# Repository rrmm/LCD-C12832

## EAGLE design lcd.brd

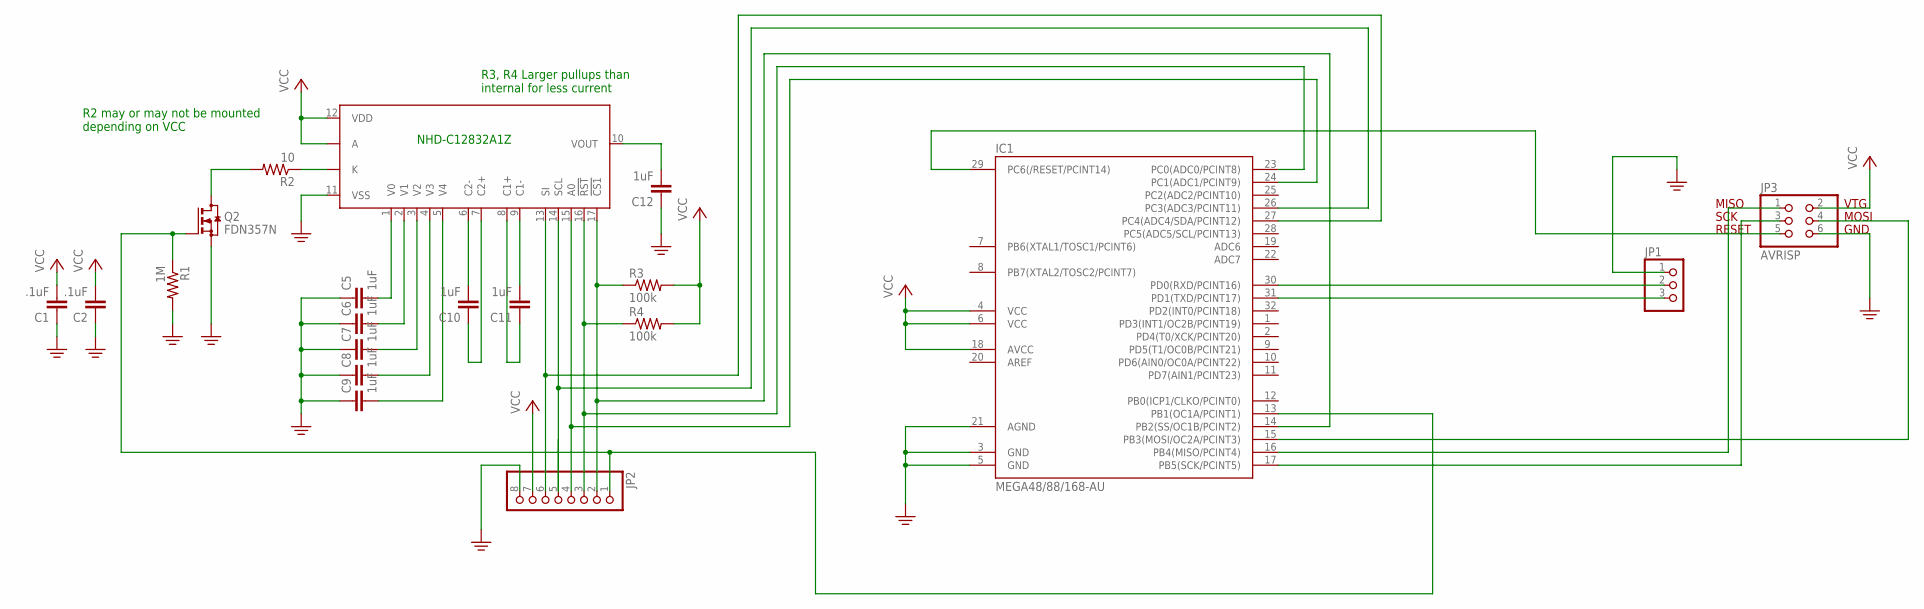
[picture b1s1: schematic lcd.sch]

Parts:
C1, C2: .1uF; C0603
C5, C6, C7, C8, C9, C10, C11, C12: 1uF; C0603
IC1: MEGA48/88/168-AU; TQFP32-08
JP1: PINHD-1X3; 1X03
JP2: PINHD-1X8; 1X08
JP3: AVRISP; 2X03
Q2: FDN357N; SOT23
R1: 1M; R0603
R2: 10; R0603
R3, R4: 100k; R0603
U$1: NHD-C12832A1Z

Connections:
GND: C1.1, C2.1, C5.1, C6.1, C7.1, C8.1, C9.1, C12.1, IC1.3 (GND), IC1.5 (GND), IC1.21 (AGND), JP1.1, JP2.8, JP3.6, Q2.2 (S), R1.2, U$1.11 (VSS)
unnamed: IC1.29 (PC6(/RESET/PCINT14)), JP3.5
unnamed: IC1.14 (PB2(SS/OC1B/PCINT2)), JP2.2, R3.1, U$1.17 (!CS1)
unnamed: IC1.23 (PC0(ADC0/PCINT8)), JP2.3, R4.1, U$1.16 (!RST)
unnamed: IC1.26 (PC3(ADC3/PCINT11)), JP2.5, U$1.14 (SCL)
unnamed: R2.1, U$1.K
unnamed: IC1.24 (PC1(ADC1/PCINT9)), JP2.4, U$1.15 (A0)
unnamed: C12.2, U$1.10 (VOUT)
unnamed: IC1.17 (PB5(SCK/PCINT5)), JP3.3
unnamed: IC1.16 (PB4(MISO/PCINT4)), JP3.1
unnamed: IC1.15 (PB3(MOSI/OC2A/PCINT3)), JP3.4
unnamed: IC1.30 (PD0(RXD/PCINT16)), JP1.2
unnamed: IC1.31 (PD1(TXD/PCINT17)), JP1.3
unnamed: IC1.27 (PC4(ADC4/SDA/PCINT12)), JP2.6, U$1.13 (SI)
unnamed: IC1.13 (PB1(OC1A/PCINT1)), JP2.1, Q2.1 (G), R1.1
unnamed: C5.2, U$1.1 (V0)
unnamed: Q2.3 (D), R2.2
unnamed: C6.2, U$1.2 (V1)
unnamed: C9.2, U$1.5 (V4)
unnamed: C7.2, U$1.3 (V2)
unnamed: C8.2, U$1.4 (V3)
unnamed: C11.1, U$1.8 (C1+)
unnamed: C10.2, U$1.6 (C2-)
unnamed: C10.1, U$1.7 (C2+)
unnamed: C11.2, U$1.9 (C1-)
VCC: C1.2, C2.2, IC1.4 (VCC), IC1.6 (VCC), IC1.18 (AVCC), JP2.7, JP3.2, R3.2, R4.2, U$1.12 (VDD), U$1.A

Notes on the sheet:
R2 may or may not be mounted depending on VCC
R3, R4 Larger pullups than internal for less current
NHD-C12832A1Z

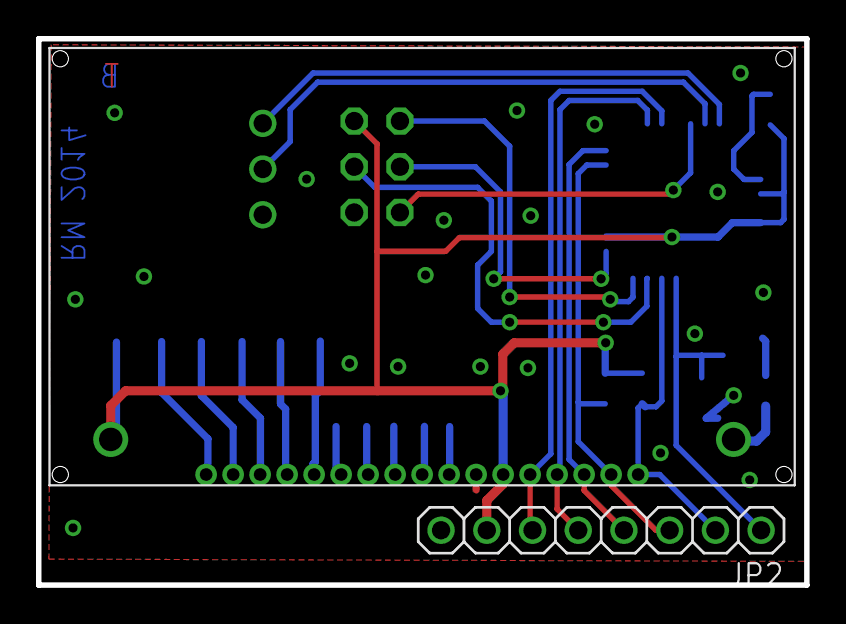
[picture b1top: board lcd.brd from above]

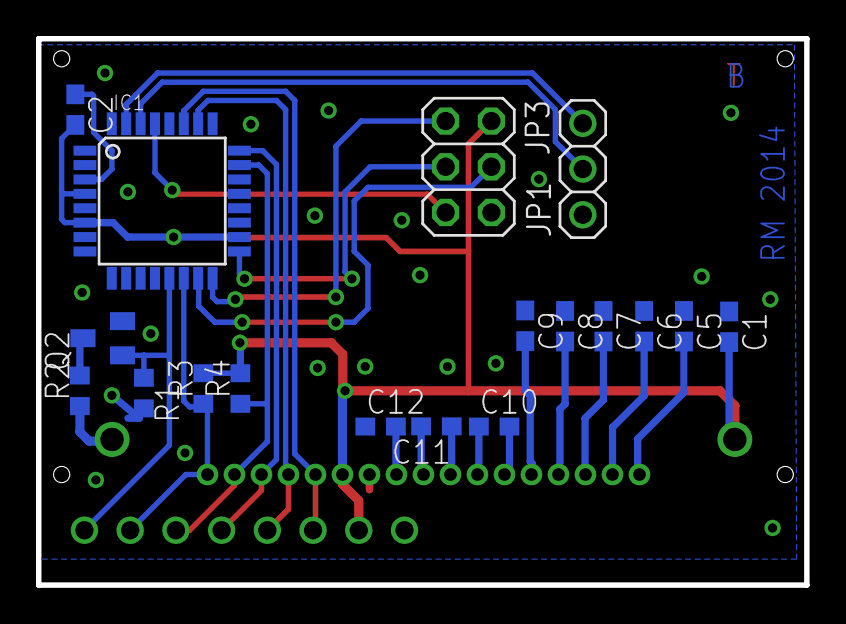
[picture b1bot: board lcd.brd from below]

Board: 2 copper layers, 42.7 x 30.4 mm, 20 parts (18 on the bottom side), 26 nets.

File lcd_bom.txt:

Partlist exported from /home/here/stuff/schematics/lcd/lcd.sch at 5/15/14 10:56 PM

Qty Value            Device           Package       Parts                             Description                
1                    NHD-C12832A1Z    NHD-C12832A1Z U$1                                                          
1                    PINHD-1X3        1X03          JP1                               PIN HEADER                 
1                    PINHD-1X8        1X08          JP2                               PIN HEADER                 
2   .1uF             C-EUC0603        C0603         C1, C2                            CAPACITOR, European symbol 
1   10               R-US_R0603       R0603         R2                                RESISTOR, American symbol  
2   100k             R-US_R0603       R0603         R3, R4                            RESISTOR, American symbol  
1   1M               R-US_R0603       R0603         R1                                RESISTOR, American symbol  
8   1uF              C-EUC0603        C0603         C5, C6, C7, C8, C9, C10, C11, C12 CAPACITOR, European symbol 
1   AVRISP           AVRISP           2X03          JP3                               AVR ISP Connector          
1   FDN357N          BSS123           SOT23         Q2                                N-CHANNEL MOS FET          
1   MEGA48/88/168-AU MEGA48/88/168-AU TQFP32-08     IC1

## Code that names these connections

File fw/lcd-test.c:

#include <util/delay.h>
#include <avr/io.h>
#include <avr/interrupt.h>
#include <avr/wdt.h>
#include <avr/sleep.h>




#include "misc.h"

#define WGM_VALUE_CTC ((1<<1)|(0<<0))
#define CS_VALUE_ON  ((0<<2)|(0<<0)|(1<<1))
#define CS_VALUE_OFF ((0<<2)|(0<<0)|(0<<0))
#define COM_CLR_VALUE  (1<<COM0A1|0<<COM0A0)
#define COM_SET_VALUE  (1<<COM0A1|1<<COM0A0)
#define COM_TGL_VALUE  (0<<COM0A1|1<<COM0A0)
#define COM_DISCONNECT_VALUE  (0<<COM0A1|0<<COM0A0)


/* 
 * clock source
 * CS02:00 = 0 off
 *           1   clk
 *           2   clk/8
 *           3   clk/64
 *           4   clk/256
 *           5   clk/1024
 */

// WGM02 is high, no prescalar
#define PWM_TCCR0B_BYTE 0x09

#define PWM_START() do { TCCR0B = PWM_TCCR0B_BYTE; } while (0)
#define PWM_STOP()  do {						\
	TCCR0A &= ~0x30;							\
	TCCR0B &= ~0x07;							\
  } while (0)

#define PWM_OUTPUT_ENABLE()  do { TCCR0A |= 0x20; } while (0)
#define PWM_OUTPUT_DISABLE() do { \
	TCCR0A &= ~0x30;			  \
  } while (0)



void
set_backlight(unsigned char i)
{
  OCR1A = 0x3ff >> (9-i);
}


inline void
pwm_init(void)
{

  // Assume 1Mhz Oscillator
  
  //PWM_STOP();
  // SET OC1A to do something, clear on compare match, set on bottom
  // in compare output mode/fast pwm mode
  // set to fast pwm 10-bit
  TCCR1A = (TCCR1A & (~0xC0|~0x03)) | 0x80 | 0x3 ;
  // clk/256, bits of wgm 
  TCCR1B = 0x09;

  // top is 0x3f
  OCR1A = 0x3ff >> 5;
  TCNT1 = 0;


  TIMSK1 = 0;  // no interrupts
  
  // clear all flags by writing 1's 
  TIFR1 = 0xff;
  TIMSK1 = BSET(TOIE0);
  
}

#define TCCR0A_WGM_CTC       2
#define TCCR0B_CLKSRC_NONE   0
#define TCCR0B_CLKSRC_1024   5


inline void 
timer_start(void)
{
  TCCR0B = TCCR0B_CLKSRC_1024;
}

void
timer_init(void)
{
  TCCR0B = TCCR0B_CLKSRC_NONE;
  TCCR0A = TCCR0A_WGM_CTC;
  TCNT0 = 0;
  OCR0A = 250;
  //TIMSK0 = BSET(TOIE0);
  TIMSK0 = BSET(OCIE0A);    
  
}


#define enable_ext_int()  do {   EIFR |= 0xff; EIMSK |= 0x01; } while (0)
#define disable_ext_int()  EIMSK &= ~0x01





 // blacklight en PB1
#define SET_BLEN(x) do { PORTB = (PORTB&(~0x02)) | (((x)&1)<<1); } while (0)

 // PC0 is RST
#define SET_RST(x)  do { PORTC = (PORTC&(~0x01)) | (((x)&1)<<0); } while (0)
 // PC1 is A0
#define SET_A0(x)   do { PORTC = (PORTC&(~0x02)) | (((x)&1)<<1); } while (0)
 // PB2 is CS
#define SET_CS(x)   do { PORTB = (PORTB&(~0x04)) | (((x)&1)<<2); } while (0)
 // PC3 is SCL
#define SET_SCL(x)  do { PORTC = (PORTC&(~0x08)) | (((x)&1)<<3); } while (0)
 // PC4 is SI
#define SET_SI(x)   do { PORTC = (PORTC&(~0x10)) | (((x)&1)<<4); } while (0)

     



void
lcd_out(unsigned char x, unsigned char is_data)
{
  unsigned char i;
  unsigned char n;
  unsigned char v;

  i = x;
  SET_CS(0);
  
  if (is_data) { 
	SET_A0(1);
  } else {
	SET_A0(0);
  }
  
  for (n = 0; n < 8; n++) { 
	v = (i & 0x80);
	v >>= 7;
	i <<= 1;
	SET_SCL(0);
	SET_SI(v);
	_delay_us(1);
	SET_SCL(1);
	//_delay_us(2);
  }
  
  SET_CS(1);
  
}


void
lcd_init()
{

  SET_RST(0);
  _delay_ms(10);
  SET_RST(1);
  _delay_ms(10);


  lcd_out(0x40, 0);
  lcd_out(0xa0, 0);
  lcd_out(0xc8, 0);
  lcd_out(0xa6, 0);
  lcd_out(0xa2, 0);
  lcd_out(0x2f, 0);
  lcd_out(0xf8, 0);
  lcd_out(0x00, 0);
  lcd_out(0x23, 0);
  lcd_out(0x81, 0);
  lcd_out(0x0a, 0);
  lcd_out(0xac, 0);
  lcd_out(0x00, 0);
  lcd_out(0xaf, 0);


  // blink the entire screen
  lcd_out(0xA5, 0);  
  _delay_ms(200);
  lcd_out(0xA4, 0);  
  /*

  lcd_out(0xA0, 0);
  lcd_out(0xAE, 0);
  lcd_out(0xC0, 0);
  lcd_out(0xA2, 0);
  lcd_out(0x2F, 0);
  lcd_out(0x26, 0);
  lcd_out(0x81, 0);
  lcd_out(0x2F, 0);
  */
  //lcd_out(0xAF, 0);
  
}

#define SET_PAGE(x)  lcd_out(0xB0 | ((x)&0x0f), 0)
#define SET_COL(x)  do {							\
  lcd_out( 0x10 | ((x)&0xf0)>>4, 0);				\
  lcd_out( 0x00 | (x)&0x0f    , 0);				\
  } while(0)	

void
clrscr(void)
{
  unsigned char i = 0; 
  SET_PAGE(0);
  SET_COL(0);
  for (i = 0; i < 128; i++) { 
	lcd_out(0x0, 1);
  }
  SET_PAGE(1);
  SET_COL(0);
  for (i = 0; i < 128; i++) { 
	lcd_out(0x0, 1);
  }
  SET_PAGE(2);
  SET_COL(0);
  for (i = 0; i < 128; i++) { 
	lcd_out(0x0, 1);
  }
  SET_PAGE(3);
  SET_COL(0);
  for (i = 0; i < 128; i++) { 
	lcd_out(0x0, 1);
  }
    
  SET_PAGE(0);
  SET_COL(0);
}


// 9600 @ 1Mhz clock

void
serial_init(void)
{

  UCSR0A = 0x2; // U2X0 = 1 double speed
  UCSR0B = (1<<RXEN0)|(1<<TXEN0);
  // UCSR0C ; // default is 8-1-N
  UBRR0 = 12; // 9600 @ 1Mhz clock
}

#include "lcd_print_char_6x8.c"


/*
 *  these take abcdXXXX -> aabbccdd
 *
 */
#define DOUBLE_HIGH_NYBBLE(c)  	  ((c & 0x80)>>0 | (c & 0x80)>>1 | \
								   (c & 0x40)>>1 | (c & 0x40)>>2 | \
								   (c & 0x20)>>2 | (c & 0x20)>>3 | \
								   (c & 0x10)>>3 | (c & 0x10)>>4)

#define DOUBLE_LOW_NYBBLE(c)  	  ((c & 0x08)<<4 | (c & 0x08)<<3 | \
								   (c & 0x04)<<3 | (c & 0x04)<<2 | \
								   (c & 0x02)<<2 | (c & 0x02)<<1 | \
								   (c & 0x01)<<1 | (c & 0x01)<<0)


unsigned char page = 0;
unsigned char col = 0;


void
lcd_print_char(unsigned char c, 
			   unsigned char r, unsigned char co,
			   unsigned char double_size)
{
  unsigned char i,j;
  unsigned char bm[6];
  unsigned char o; 
  char_get_bitmap(c, bm);
  SET_PAGE(r);
  SET_COL(co);
  for (i = 0; i < 6; i++) { 
	if (double_size) { 
	  o = DOUBLE_LOW_NYBBLE(bm[i]);
	} else { 
	  o = bm[i];
	}

	lcd_write(DATA, o);

	if (double_size) { 
	  lcd_write(DATA, o);
	}
  }

  if (double_size) { 
	SET_PAGE(r+1);
	SET_COL(co);
	for (i = 0; i < 6; i++) { 
	  o = DOUBLE_HIGH_NYBBLE(bm[i]);
	  
	  lcd_write(DATA, o);
	  lcd_write(DATA, o);
	}
  }

}



int
main(void)
{ 
  wdt_disable();

  
  serial_init();
  pwm_init();
  PORTC = 0x01;
  DDRC = DIR_OUT(0)|DIR_OUT(1)|DIR_OUT(3)|DIR_OUT(4);


  DDRB = DIR_OUT(1) | DIR_OUT(2);
  PORTB = 0x6;


  lcd_init();
  unsigned char i;
  unsigned char v = 0x20;


  unsigned short blc  = 0;
  unsigned short blv  = 9;
  
  unsigned char double_size = 0;
  clrscr();
  SET_PAGE(0);
  SET_COL(0);

  set_backlight(blv);

  while (1) { 
	char c;
	while (! (UCSR0A & (1<<RXC0)));
	c = UDR0;
	
	switch(c) {
	case 0x0c: // FF
	  col = 0;
	  page = 0;
	  clrscr();
	  break;
	case 0x08:
	  if (col > 0) col-= 6+double_size*5;
	  lcd_print_char(' ', page, col, double_size);
	  break;
	case '\r':
	  page+= 1 + double_size;
	  col = 0;
	  break;
	case 0x07:
	  double_size = (double_size+1)%2;
	  break;
	case 0x1b:
	  // backlight down
	  if (blv > 0) {
		blv--;
		set_backlight(blv);
	  }
	  break;
	case 0x1d:
	  // backlight up
	  if (blv < 10) {
		blv++;
		set_backlight(blv);
	  }
	  break;
	default:
	  lcd_print_char(c, page, col, double_size);
	  
	  col+=6+double_size*5;
	}

  }
  return 0;
}

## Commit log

2015-01-03 init import
2015-01-06 adding firmware to test exercise the board
2015-01-07 adding some crude double-sized text; changed the way the font info is stored
2015-01-08 more double sized character stuff
